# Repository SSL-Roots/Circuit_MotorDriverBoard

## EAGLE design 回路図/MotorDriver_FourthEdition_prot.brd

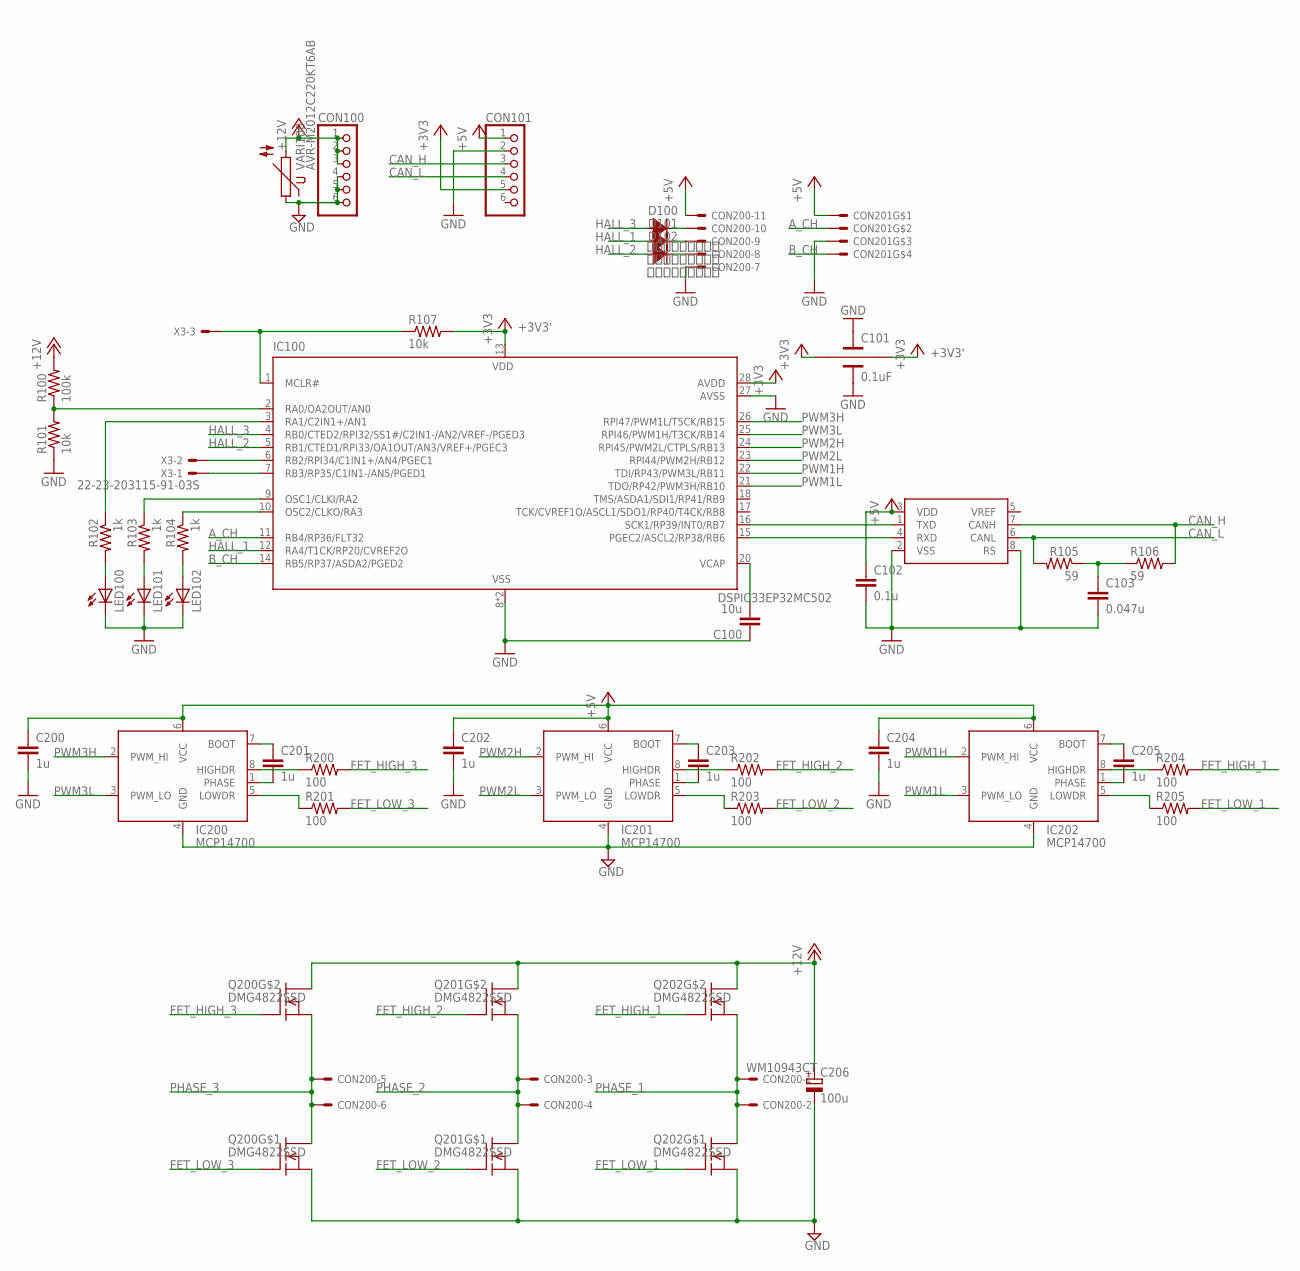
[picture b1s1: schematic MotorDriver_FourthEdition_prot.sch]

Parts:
C100: 10u; C2012
C101: 0.1uF; CKD610JB
C102: 0.1u; C1608
C103: 0.047u; C1608
C200, C201, C202, C203, C204, C205: 1u; C1608
C206: 100u; E15-5RS
CON100, CON101: PINHD-1X6S; 1X06S
CON200: WM10943CT; 52207-1185
CON201: 4B-XH-AS4B; S4B-XH-A
D100, D101, D102: ＲＢ７５１Ｓ－４０; 1608
IC100: DSPIC33EP32MC502; SOIC-28
IC101: MCP2551; SOIC-8
IC200, IC201, IC202: MCP14700; SOIC-8
LED100, LED101, LED102: LEDCHIPLED_0805; CHIPLED_0805
Q200, Q201, Q202: DMG4822SSD; SO-8
R100: 100k; R1608
R101, R107: 10k; R1608
R102, R103, R104: 1k; R1608
R105, R106: 59; R1608
R200, R201, R202, R203, R204, R205: 100; R1608
VARI100: AVR-M2012C220KT6AB; CT/CN0603
X3: 22-23-203115-91-03S; 15-91-03S

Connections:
+3V3: C101.2 (IN), CON101.5
+3V3': C101.1 (OUT), IC100.13 (VDD), IC100.28 (AVDD), R107.2
+5V: C102.1, C200.1, C202.1, C204.1, CON101.1, CON200.11, CON201.1, IC101.3 (VDD), IC200.6 (VCC), IC201.6 (VCC), IC202.6 (VCC)
+12V: C206.+, CON100.1, CON100.2, CON100.3, Q200.7 (D), Q200.8 (D), Q201.7 (D), Q201.8 (D), Q202.7 (D), Q202.8 (D), R100.2, VARI100.2
AGND: C100.1, C101.3 (GND), C101.4 (GND1), C102.2, C103.2, CON101.2, CON200.7, CON201.3, IC100.8 (VSS), IC100.19 (VSS), IC100.27 (AVSS), IC101.2 (VSS), IC101.8 (RS), LED100.C, LED101.C, LED102.C, R101.1
A_CH: CON201.2, IC100.11 (RB4/RP36/FLT32)
B_CH: CON201.4, IC100.14 (RB5/RP37/ASDA2/PGED2)
CAN_H: CON101.3, IC101.7 (CANH), R106.2
CAN_L: CON101.4, IC101.6 (CANL), R105.2
FET_HIGH_1: Q202.2 (G), R204.2
FET_HIGH_2: Q201.2 (G), R202.2
FET_HIGH_3: Q200.2 (G), R200.2
FET_LOW_1: Q202.4 (G), R205.2
FET_LOW_2: Q201.4 (G), R203.2
FET_LOW_3: Q200.4 (G), R201.2
HALL_1: D101.A, IC100.12 (RA4/T1CK/RP20/CVREF2O)
HALL_2: D102.A, IC100.5 (RB1/CTED1/RPI33/OA1OUT/AN3/VREF+/PGEC3)
HALL_3: D100.A, IC100.4 (RB0/CTED2/RPI32/SS1#/C2IN1-/AN2/VREF-/P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)
unnamed: IC100.1 (MCLR#), R107.1, X3.3
unnamed: C201.1, IC200.7 (BOOT)
unnamed: IC100.3 (RA1/C2IN1+/AN1), R102.1
unnamed: C203.1, IC201.7 (BOOT)
unnamed: IC100.7 (RB3/RP35/C1IN1-/AN5/PGED1), X3.1
unnamed: IC100.2 (RA0/OA2OUT/AN0), R100.1, R101.2
unnamed: C205.1, IC202.7 (BOOT)
unnamed: IC100.6 (RB2/RPI34/C1IN1+/AN4/PGEC1), X3.2
unnamed: C103.1, R105.1, R106.1
unnamed: CON200.10, D100.C
unnamed: CON200.9, D101.C
unnamed: CON200.8, D102.C
unnamed: IC100.16 (SCK1/RP39/INT0/RB7), IC101.1 (TXD)
unnamed: IC100.15 (PGEC2/ASCL2/RP38/RB6), IC101.4 (RXD)
unnamed: IC200.8 (HIGHDR), R200.1
unnamed: IC200.5 (LOWDR), R201.1
unnamed: IC201.8 (HIGHDR), R202.1
unnamed: IC201.5 (LOWDR), R203.1
unnamed: IC100.9 (OSC1/CLKI/RA2), R103.1
unnamed: LED100.A, R102.2
unnamed: IC202.8 (HIGHDR), R204.1
unnamed: IC202.5 (LOWDR), R205.1
unnamed: IC100.10 (OSC2/CLKO/RA3), R104.1
unnamed: C100.2, IC100.20 (VCAP)
unnamed: LED101.A, R103.2
unnamed: LED102.A, R104.2
PGND: C200.2, C202.2, C204.2, C206.-, CON100.4, CON100.5, CON100.6, IC200.4 (GND), IC201.4 (GND), IC202.4 (GND), Q200.3 (S), Q201.3 (S), Q202.3 (S), VARI100.1
PHASE_1: C205.2, CON200.1, CON200.2, IC202.1 (PHASE), Q202.1 (S), Q202.5 (D), Q202.6 (D)
PHASE_2: C203.2, CON200.3, CON200.4, IC201.1 (PHASE), Q201.1 (S), Q201.5 (D), Q201.6 (D)
PHASE_3: C201.2, CON200.5, CON200.6, IC200.1 (PHASE), Q200.1 (S), Q200.5 (D), Q200.6 (D)
PWM1H: IC100.22 (TDI/RP43/PWM3L/RB11), IC202.2 (PWM_HI)
PWM1L: IC100.21 (TDO/RP42/PWM3H/RB10), IC202.3 (PWM_LO)
PWM2H: IC100.24 (RPI45/PWM2L/CTPLS/RB13), IC201.2 (PWM_HI)
PWM2L: IC100.23 (RPI44/PWM2H/RB12), IC201.3 (PWM_LO)
PWM3H: IC100.26 (RPI47/PWM1L/T5CK/RB15), IC200.2 (PWM_HI)
PWM3L: IC100.25 (RPI46/PWM1H/T3CK/RB14), IC200.3 (PWM_LO)

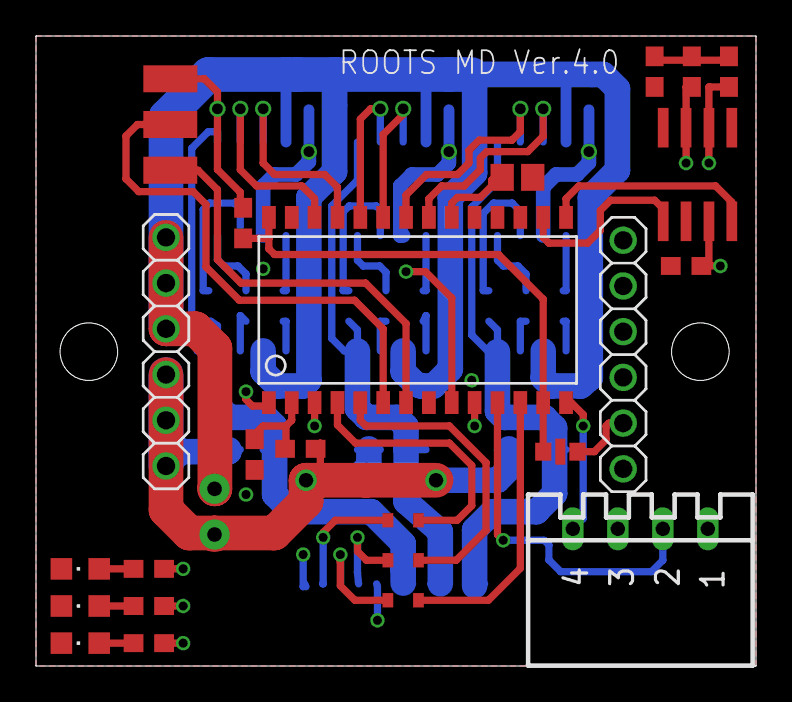
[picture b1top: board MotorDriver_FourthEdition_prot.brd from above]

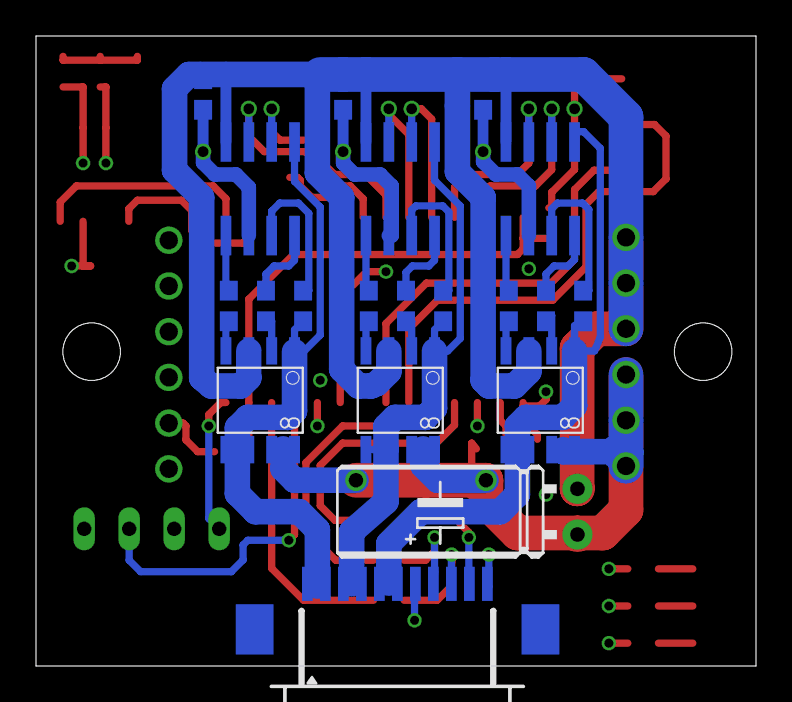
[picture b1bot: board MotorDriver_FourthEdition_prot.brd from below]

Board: 4 copper layers, 40.0 x 35.0 mm, 45 parts (19 on the bottom side), 54 nets.
